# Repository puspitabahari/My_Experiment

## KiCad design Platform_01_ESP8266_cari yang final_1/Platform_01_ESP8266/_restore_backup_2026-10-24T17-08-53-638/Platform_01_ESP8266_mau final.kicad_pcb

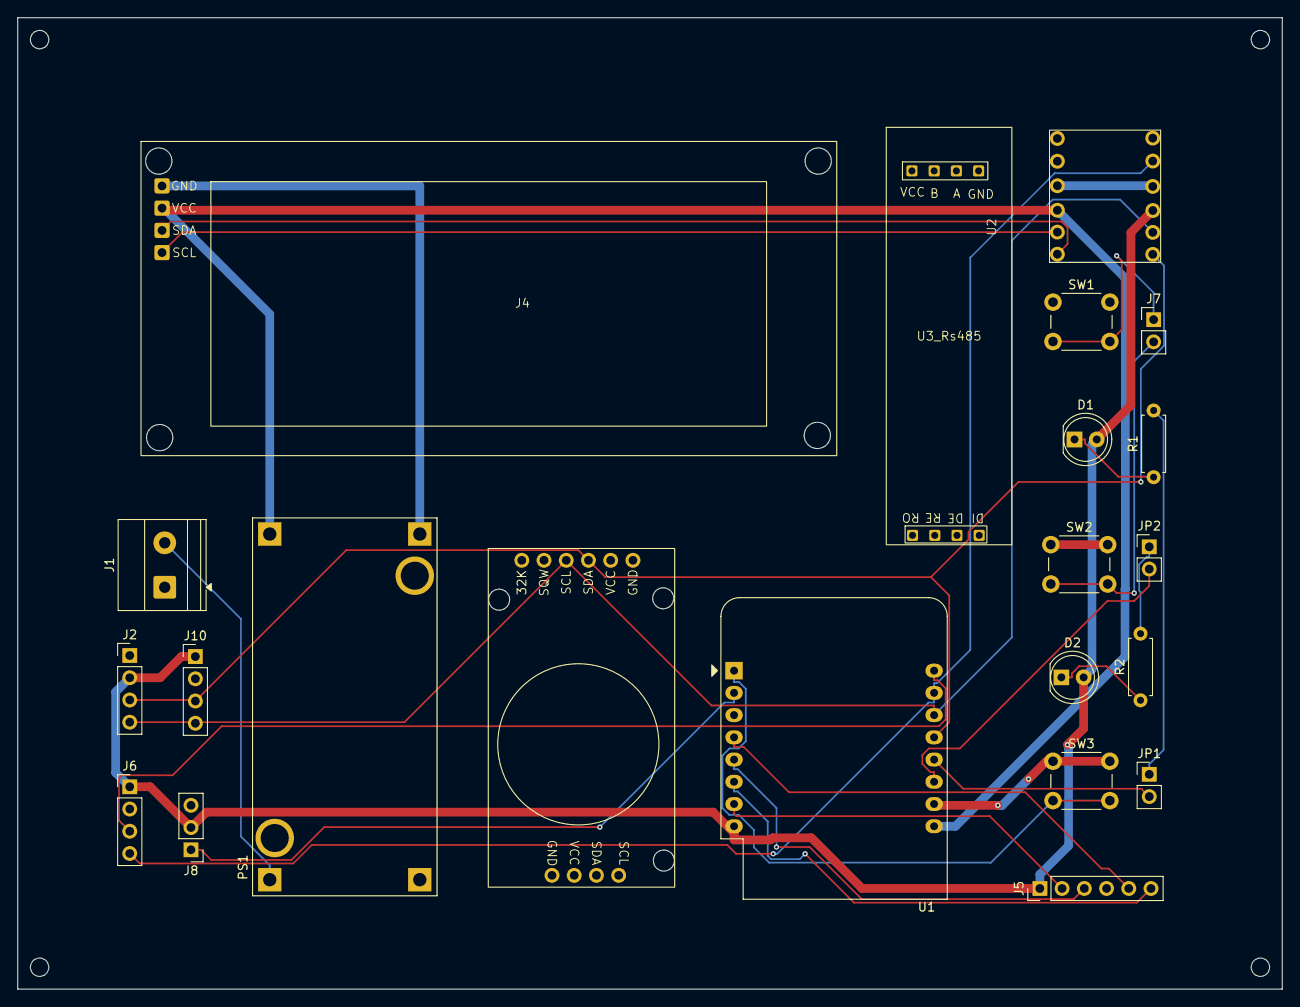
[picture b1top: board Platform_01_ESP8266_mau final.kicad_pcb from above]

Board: 2 copper layers, 144.5 x 111.0 mm, 26 parts (0 on the bottom side), 24 nets.

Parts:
D1, D2: LED; LED_D5.0mm
J1: POWER_IN; TerminalBlock_Phoenix_MKDS-1,5-2-5.08_1x02_P5.08mm_Horizont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
J2: I2C_Port; PinHeader_1x04_P2.54mm_Vertical
J4: LCD; LCDI2C_Module
J5: SPI; PinHeader_1x06_P2.54mm_Vertical
J6: SERIAL_PORT; PinHeader_1x04_P2.54mm_Vertical
J7: Conn_01x02; PinHeader_1x02_P2.54mm_Vertical
J8: ADC_PORT; PinHeader_1x03_P2.54mm_Vertical
J9: RTC; RTC_DS3231_Module
J10: J_PCF8574; PinHeader_1x04_P2.54mm_Vertical
JP1, JP2: SolderJumper_2_Open; PinHeader_1x02_P2.54mm_Vertical
PS1: LM2596_Module; CONV_MC00100
R1, R2: 220; R_Axial_DIN0207_L6.3mm_D2.5mm_P7.62mm_Horizontal
SW1, SW2, SW3: SW_Push; SW_PUSH_6mm_H5mm
U1: WEMOS_D1_mini; WEMOS_D1_mini_light
U2: level_converter
U3_Rs485: RS485_Footprint
a: MountingHole_2.1mm
b: MountingHole_2.1mm
c: MountingHole_2.1mm
d: MountingHole_2.1mm

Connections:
+3V3: D1.2 (A), D2.2 (A), J2.2, J5.1, J6.1, J8.2, J10.1, U1.8 (3V3), U2.9 (LV)
+5V: J4.2, PS1.OUT+, U1.9 (5V), U2.3 (HV)
/<NO NET>: SW3.2, U1.1 (~RST)
/ADC_A0: J8.1, U1.2 (A0)
/BTN1_CTRL: J7.1, SW1.2
/BTN2_CTRL: J7.2, SW2.2
/I2C_SCL: J2.4, J9.SCL (Pin_2), J10.4, U1.14 (SCL/D1), U2.8 (LV2)
/I2C_SDA: J2.3, J9.SDA (Pin_1), J10.3, U1.13 (SDA/D2), U2.7 (LV1)
/LCD_SCL_5V: J4.4, U2.2 (HV2)
/LCD_SDA_5V: J4.3, U2.1 (HV1)
/LED1_CTRL: JP1.2 (B), U1.12 (D3)
/LED2_CTRL: JP2.2 (B), U1.11 (D4)
/POWER_IN+: J1.2, PS1.IN+
/SPI_CS: J5.2, U1.7 (CS/D8)
/SPI_MISO: J5.3, U1.5 (MISO/D6)
/SPI_MOSI: J5.6, U1.6 (MOSI/D7)
/SPI_SCK: J5.5, U1.4 (SCK/D5)
/UART_RX: J6.4, U1.15 (RX), U2.11 (LV3)
/UART_TX: J6.3, U1.16 (TX)
GND: J1.1, J2.1, J4.1, J5.4, J6.2, J8.3, J9.GND (Pin_4), J10.2, PS1.IN-, PS1.OUT-, SW1.1, SW2.1, SW3.1, U1.10 (GND), U2.4 (GND), U2.10 (GND)
unnamed: D1.1 (K), R1.1
unnamed: D2.1 (K), R2.1
unnamed: JP1.1 (A), R1.2
unnamed: JP2.1 (A), R2.2

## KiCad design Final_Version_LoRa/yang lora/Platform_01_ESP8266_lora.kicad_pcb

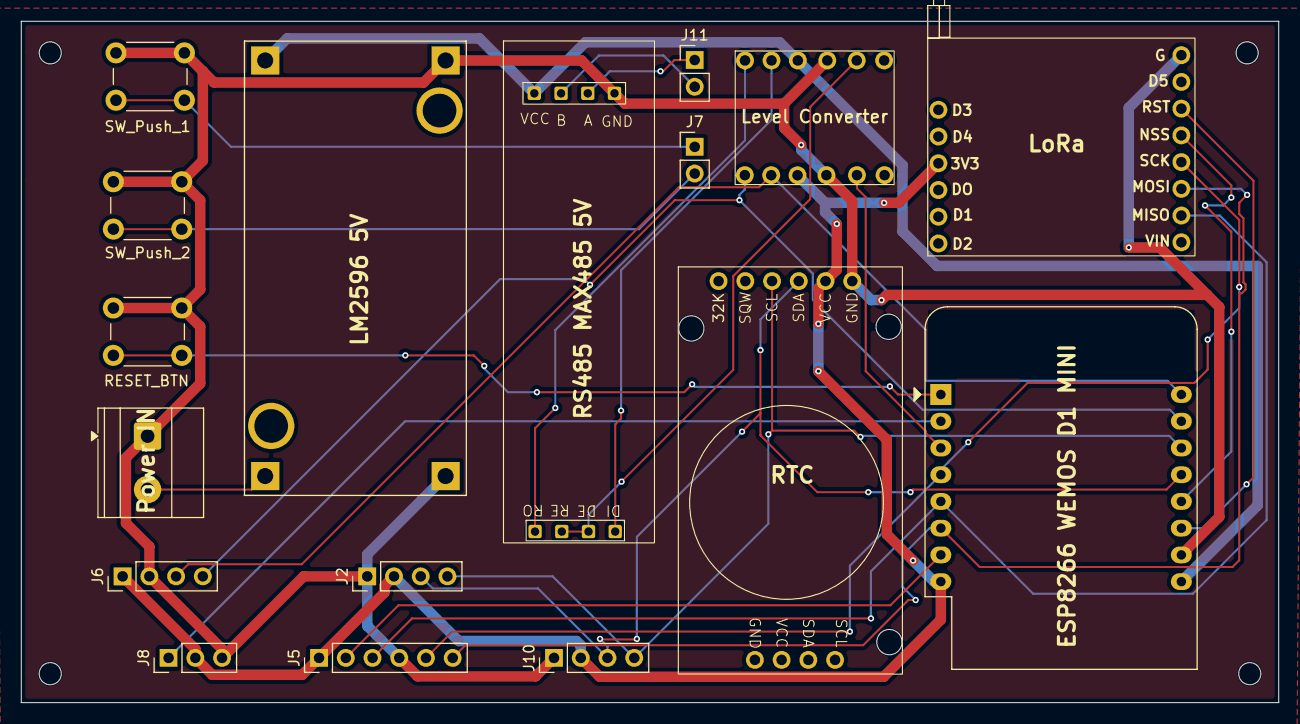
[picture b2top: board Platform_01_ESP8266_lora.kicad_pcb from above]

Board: 2 copper layers, 119.5 x 64.8 mm, 21 parts (0 on the bottom side), 24 nets.

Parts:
J1: POWER_IN; TerminalBlock_Phoenix_MKDS-1,5-2-5.08_1x02_P5.08mm_Horizont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
J2: I2C_Port; PinHeader_1x04_P2.54mm_Vertical
J5: SPI; PinHeader_1x06_P2.54mm_Vertical
J6: SERIAL_PORT; PinHeader_1x04_P2.54mm_Vertical
J7, J11: Conn_01x02; PinHeader_1x02_P2.54mm_Vertical
J8: ADC_PORT; PinHeader_1x03_P2.54mm_Vertical
J9: RTC; RTC_DS3231_Module
J10: J_PCF8574; PinHeader_1x04_P2.54mm_Vertical
PS1: LM2596_Module; CONV_MC00100
SW1: SW_Push_1; SW_PUSH_6mm_H5mm
SW2: SW_Push_2; SW_PUSH_6mm_H5mm
SW3: SW_Push; SW_PUSH_6mm_H5mm
U1: WEMOS_D1_mini; WEMOS_D1_mini_light
U2: LoRa
U3_Rs485: RS485_Footprint
U5_Level_RS485: level_converter
mounting1, mounting2, mounting3, mounting4: MountingHole_2.1mm

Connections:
+3V3: J2.2, J5.1, J6.1, J8.2, J9.3V3 (Pin_3), J10.2, U1.8 (3V3), U2.11 (3V3), U5_Level_RS485.9 (LV)
+5V: PS1.OUT+, U1.9 (5V), U3_Rs485.VCC, U5_Level_RS485.3 (HV)
/<NO NET>: SW3.2, U1.1 (~RST)
/ADC_A0: J8.1, U1.2 (A0)
/BTN1_CTRL: J7.1, SW1.2
/BTN2_CTRL: J7.2, SW2.2
/I2C_SCL: J2.4, J9.SCL (Pin_2), J10.4, U1.14 (SCL/D1)
/I2C_SDA: J2.3, J9.SDA (Pin_1), J10.3, U1.13 (SDA/D2)
/LORA_NSS: U1.12 (D3), U2.4 (NSS)
/LORA_RST: U1.11 (D4), U2.3 (RST)
/POWER_IN+: J1.2, PS1.IN+
/RS485_A: J11.1, U3_Rs485.A
/RS485_B: J11.2, U3_Rs485.B
/RS485_DI_5V: U3_Rs485.DI, U5_Level_RS485.2 (HV2)
/RS485_EN: U1.3 (D0), U5_Level_RS485.11 (LV3)
/RS485_EN_5V: U3_Rs485.DE, U3_Rs485.RE, U5_Level_RS485.5 (HV3)
/RS485_RO_5V: U3_Rs485.RO, U5_Level_RS485.1 (HV1)
/SPI_CS: J5.2, U1.7 (CS/D8)
/SPI_MISO: J5.3, U1.5 (MISO/D6), U2.7 (MISO)
/SPI_MOSI: J5.6, U1.6 (MOSI/D7), U2.6 (MOSI)
/SPI_SCK: J5.5, U1.4 (SCK/D5), U2.5 (SCK)
/UART_RX: J6.4, U1.15 (RX), U5_Level_RS485.7 (LV1)
/UART_TX: J6.3, U1.16 (TX), U5_Level_RS485.8 (LV2)
GND: J1.1, J2.1, J5.4, J6.2, J8.3, J9.GND (Pin_4), J10.1, PS1.IN-, PS1.OUT-, SW1.1, SW2.1, SW3.1, U1.10 (GND), U2.1 (G), U3_Rs485.GND, U5_Level_RS485.4 (GND), U5_Level_RS485.10 (GND)

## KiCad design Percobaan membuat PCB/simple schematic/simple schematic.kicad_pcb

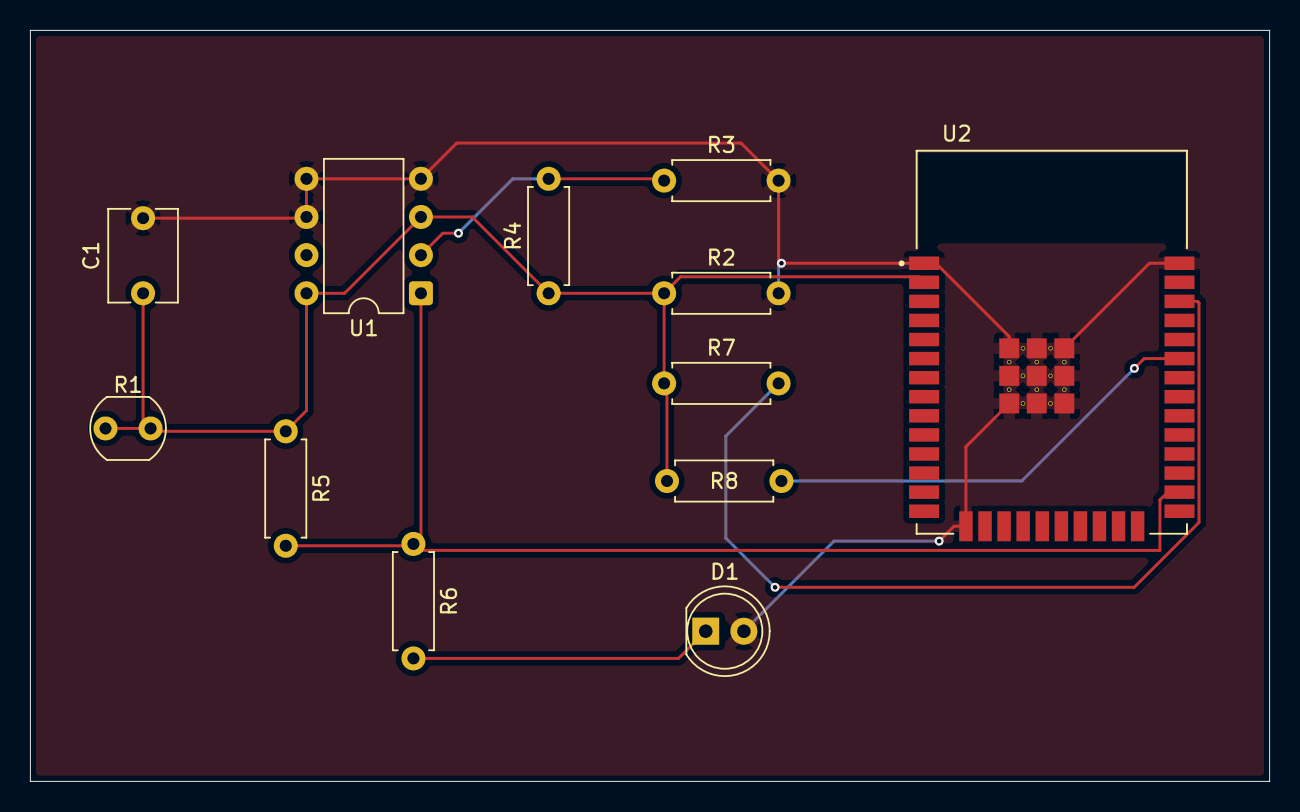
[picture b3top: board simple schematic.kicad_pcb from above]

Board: 2 copper layers, 82.5 x 50.0 mm, 12 parts (0 on the bottom side), 7 nets.

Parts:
C1: 100nF; C_Disc_D6.0mm_W4.4mm_P5.00mm
D1: LED; LED_D5.0mm
R1: GL5528; R_LDR_5.0x4.1mm_P3mm_Vertical
R2, R3, R4, R5: 10K; R_Axial_DIN0207_L6.3mm_D2.5mm_P7.62mm_Horizontal
R6: 330R; R_Axial_DIN0207_L6.3mm_D2.5mm_P7.62mm_Horizontal
R7, R8: 4.7K; R_Axial_DIN0207_L6.3mm_D2.5mm_P7.62mm_Horizontal
U1: LM393; DIP-8_W7.62mm
U2: ESP32-WROOM-32; MODULE_ESP32-WROOM-32

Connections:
+3V3: C1.1, R1.1, R1.2, R2.1, R4.1, R5.1, R7.1, R8.1, U1.3 (+), U1.8 (V+), U2.2 (3V3)
/SCL: R7.2, U2.36 (IO22)
/SDA: R8.2, U2.33 (IO21)
GND: C1.2, D1.2 (A), R2.2, R3.2, U1.4 (V-), U1.5 (+), U1.6 (-), U2.1 (GND), U2.15 (GND), U2.38 (GND), U2.39_1 (GND), U2.39_2 (GND), U2.39_3 (GND), U2.39_4 (GND), U2.39_5 (GND), U2.39_6 (GND), U2.39_7 (GND), U2.39_8 (GND), U2.39_9 (GND), U2.39_10 (GND), U2.39_11 (GND), U2.39_12 (GND), U2.39_13 (GND), U2.39_14 (GND), U2.39_15 (GND), U2.39_16 (GND), U2.39_17 (GND), U2.39_18 (GND), U2.39_19 (GND), U2.39_20 (GND), U2.39_21 (GND)
unnamed: D1.1 (K), R6.2
unnamed: R3.1, R4.2, U1.2 (-)
unnamed: R5.2, R6.1, U1.1, U2.26 (IO4)

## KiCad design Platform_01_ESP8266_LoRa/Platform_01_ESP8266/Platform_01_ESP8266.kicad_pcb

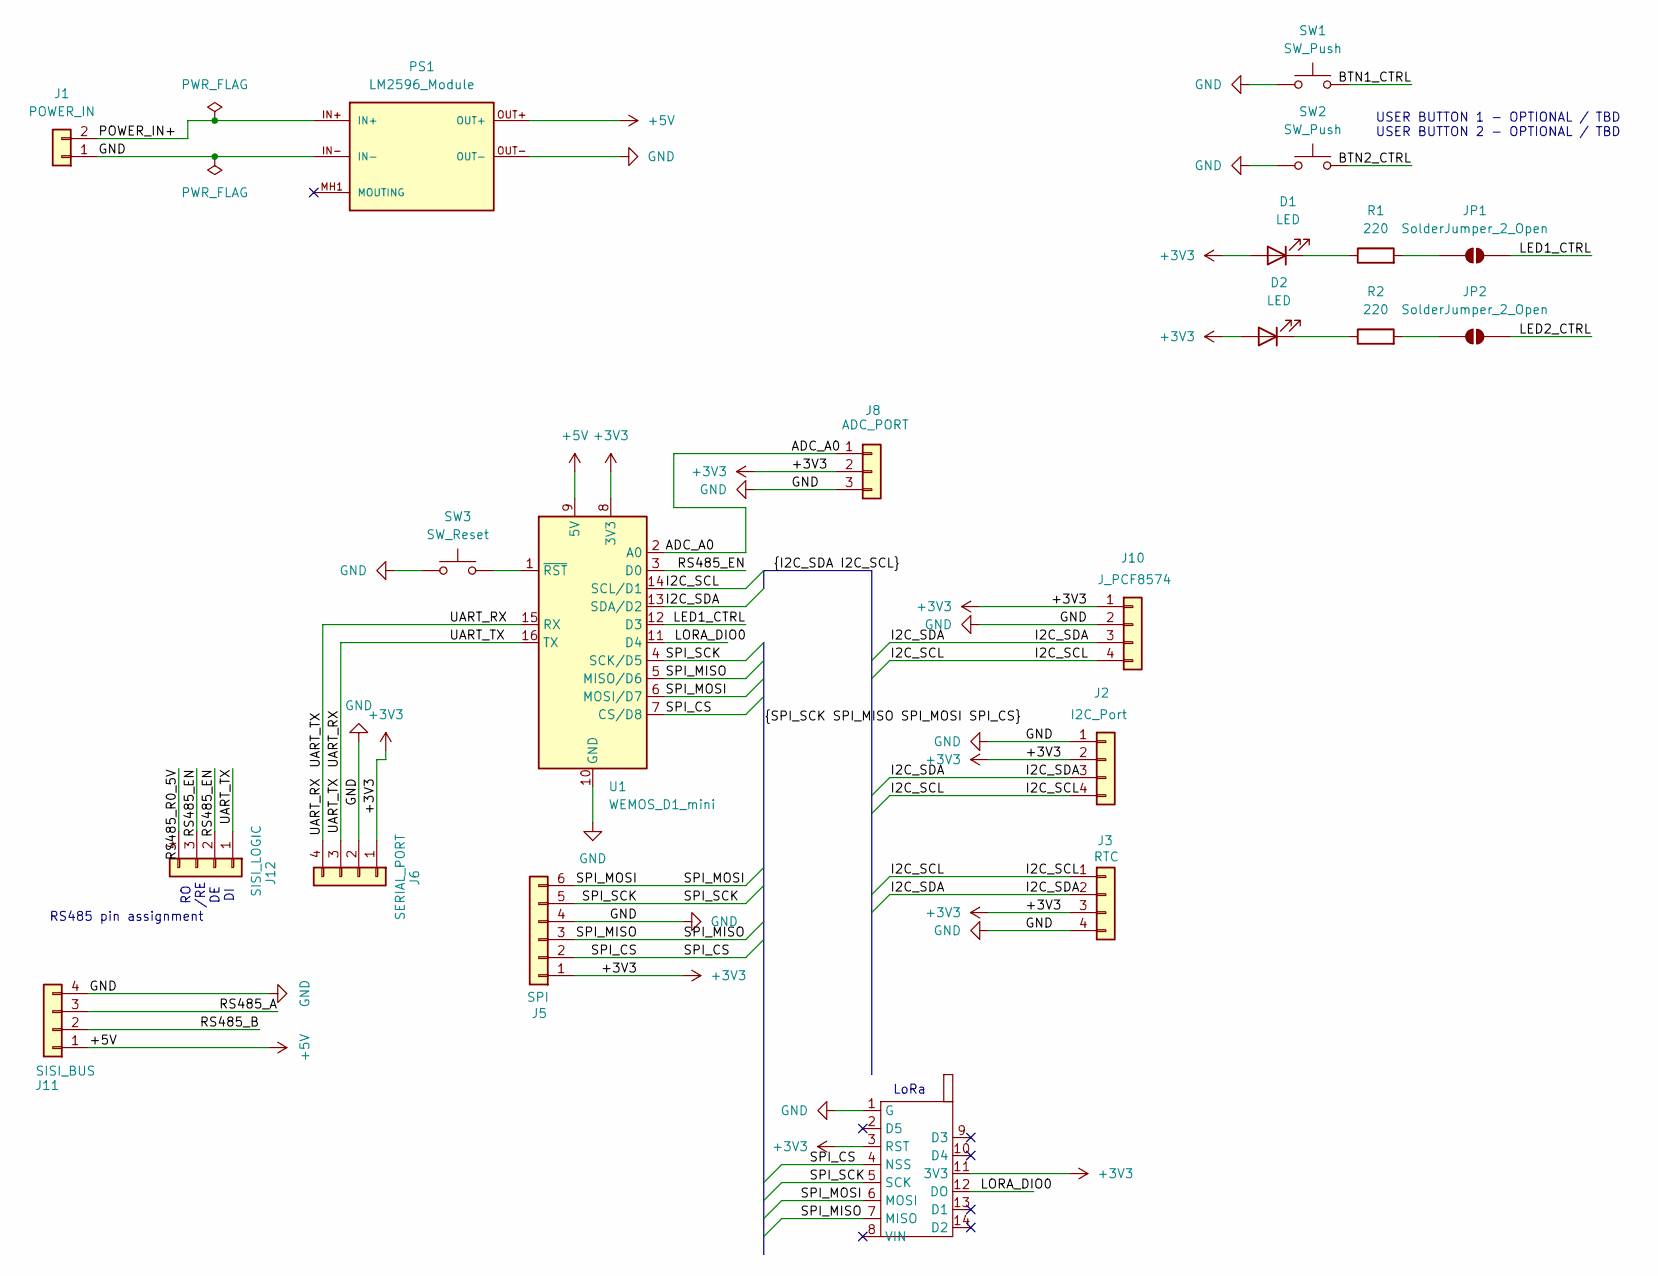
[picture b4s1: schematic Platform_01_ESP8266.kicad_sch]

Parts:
D1, D2: LED; LED_D5.0mm
J1: POWER_IN; TerminalBlock_Phoenix_MKDS-1,5-2-5.08_1x02_P5.08mm_Horizont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
J2: I2C_Port; PinHeader_1x04_P2.54mm_Vertical
J3: RTC; RTC_DS3231_Module
J5: SPI; PinHeader_1x06_P2.54mm_Vertical
J6: SERIAL_PORT; PinHeader_1x04_P2.54mm_Vertical
J8: ADC_PORT; PinHeader_1x03_P2.54mm_Vertical
J10: J_PCF8574; PinHeader_1x04_P2.54mm_Vertical
J11: SISI_BUS; TerminalBlock_Phoenix_MKDS-1,5-4-5.08_1x04_P5.08mm_Horizont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
J12: SISI_LOGIC; PinHeader_1x04_P2.54mm_Vertical
JP1, JP2: SolderJumper_2_Open; PinHeader_1x02_P2.54mm_Vertical
PS1: LM2596_Module; CONV_MC00100; PARTREV NA
R1, R2: 220; R_Axial_DIN0207_L6.3mm_D2.5mm_P7.62mm_Horizontal
SW1, SW2: SW_Push; SW_PUSH_6mm_H5mm
SW3: SW_Reset; SW_PUSH_6mm
U1: WEMOS_D1_mini; WEMOS_D1_mini_light
U3: LoRa

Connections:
+3V3: D1.2 (A), D2.2 (A), J2.2, J3.3, J5.1, J6.1, J8.2, J10.1, U1.8 (3V3), U3.3 (RST), U3.11 (3V3)
+5V: J11.1, PS1.OUT+, U1.9 (5V)
/<NO NET>: SW3.2, U1.1 (~RST)
/ADC_A0: J8.1, U1.2 (A0)
/BTN1_CTRL: SW1.2
/BTN2_CTRL: SW2.2
/I2C_SCL: J2.4, J3.1, J10.4, U1.14 (SCL/D1)
/I2C_SDA: J2.3, J3.2, J10.3, U1.13 (SDA/D2)
/LED1_CTRL: JP1.2 (B), U1.12 (D3)
/LED2_CTRL: JP2.2 (B)
/LORA_DIO0: U1.11 (D4), U3.12 (DO)
/POWER_IN+: J1.2, PS1.IN+
/RS485_A: J11.3
/RS485_B: J11.2
/RS485_EN: J12.2, J12.3, U1.3 (D0)
/RS485_R0_5V: J12.4
/SPI_CS: J5.2, U1.7 (CS/D8), U3.4 (NSS)
/SPI_MISO: J5.3, U1.5 (MISO/D6), U3.7 (MISO)
/SPI_MOSI: J5.6, U1.6 (MOSI/D7), U3.6 (MOSI)
/SPI_SCK: J5.5, U1.4 (SCK/D5), U3.5 (SCK)
/UART_RX: J6.3, J6.4, J12.1, U1.15 (RX), U1.16 (TX)
GND: J1.1, J2.1, J3.4, J5.4, J6.2, J8.3, J10.2, J11.4, PS1.IN-, PS1.OUT-, SW1.1, SW2.1, SW3.1, U1.10 (GND), U3.1 (G)
unnamed: D1.1 (K), R1.1
unnamed: D2.1 (K), R2.1
unnamed: JP1.1 (A), R1.2
unnamed: JP2.1 (A), R2.2

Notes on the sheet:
RO /RE DE DI
RS485 pin assignment
LoRa
USER BUTTON 1 - OPTIONAL / TBD USER BUTTON 2 - OPTIONAL / TBD

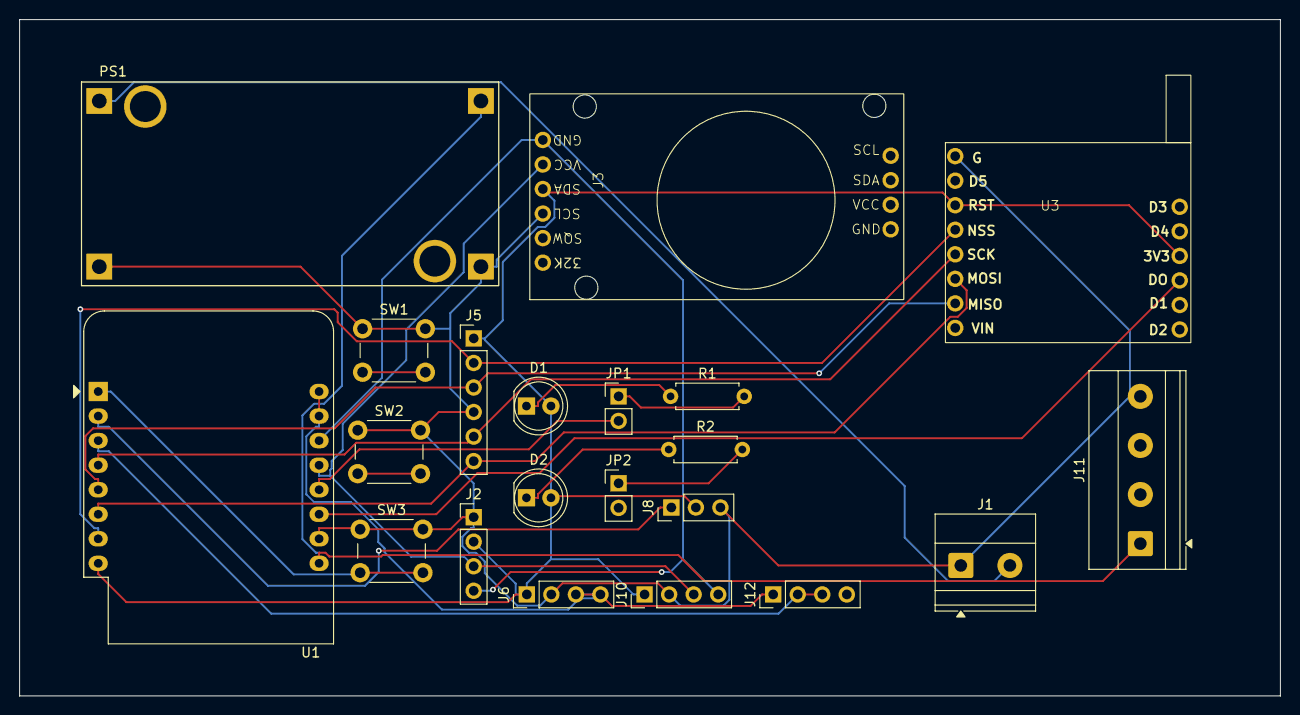
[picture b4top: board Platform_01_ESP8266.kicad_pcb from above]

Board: 2 copper layers, 130.5 x 70.0 mm, 21 parts (0 on the bottom side), 20 nets.

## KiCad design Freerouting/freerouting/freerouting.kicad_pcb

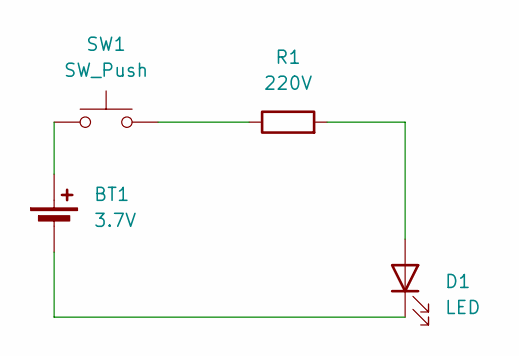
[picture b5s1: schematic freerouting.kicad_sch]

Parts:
BT1: 3.7V; Battery_Panasonic_CR1025-VSK_Vertical_CircularHoles
D1: LED; LED_D5.0mm-4_RGB_Wide_Pins
R1: 220V; R_Bare_Metal_Element_L16.3mm_W4.8mm_P15.30mm
SW1: SW_Push; SW_TH_Tactile_Omron_B3F-100x

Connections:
unnamed: BT1.1 (+), SW1.1
unnamed: BT1.2 (-), D1.1 (K)
unnamed: D1.2 (A), R1.2
unnamed: R1.1, SW1.2

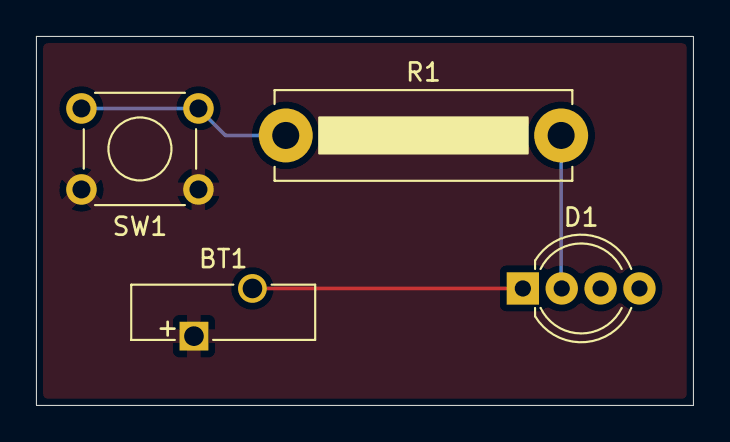
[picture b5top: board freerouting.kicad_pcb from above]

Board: 2 copper layers, 36.5 x 20.5 mm, 4 parts (0 on the bottom side), 4 nets.
